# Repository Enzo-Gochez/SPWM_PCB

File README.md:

# SPWM_PCB
A high-precision SPWM control signal generator based on ICL8038 and LT1014. Developed using KiCad, the design includes signal generation, comparison stages, and a robust PCB layout.

Schematic view

PCB layout view

Simulated digital oscilloscope view

3D view

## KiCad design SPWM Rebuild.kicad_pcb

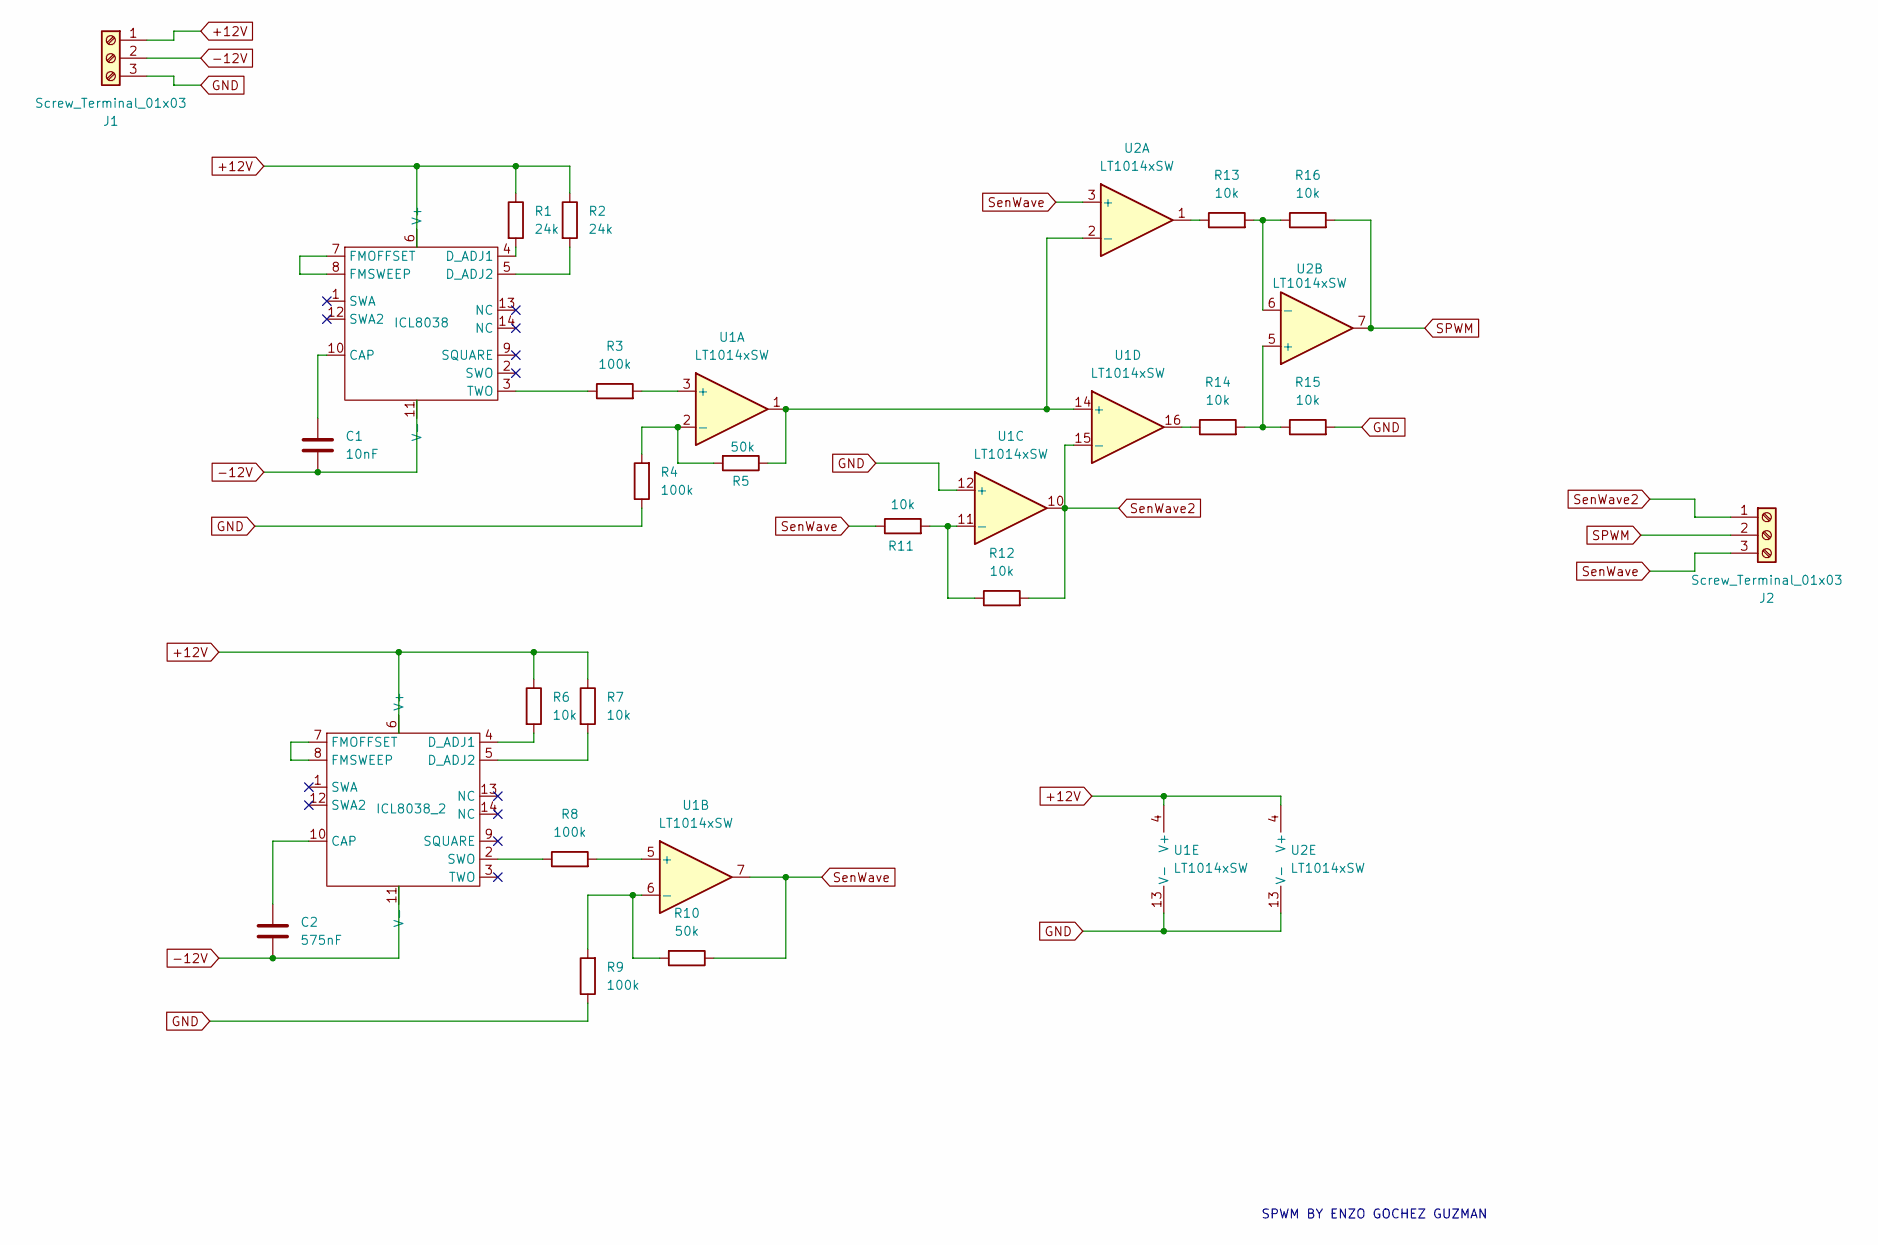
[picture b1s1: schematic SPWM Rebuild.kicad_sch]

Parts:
C1: 10nF; C_Radial_D4.0mm_H7.0mm_P1.50mm
C2: 575nF; C_Radial_D4.0mm_H7.0mm_P1.50mm
ICL8038, ICL8038_2: DIP-14_W7.62mm
J1, J2: Screw_Terminal_01x03; TerminalBlock_Xinya_XY308-2.54-3P_1x03_P2.54mm_Horizontal
R1, R2: 24k; R_Axial_DIN0204_L3.6mm_D1.6mm_P7.62mm_Horizontal
R3, R4, R8, R9: 100k; R_Axial_DIN0204_L3.6mm_D1.6mm_P7.62mm_Horizontal
R5, R10: 50k; R_Axial_DIN0204_L3.6mm_D1.6mm_P7.62mm_Horizontal
R6, R7, R11, R12, R13, R14, R15, R16: 10k; R_Axial_DIN0204_L3.6mm_D1.6mm_P7.62mm_Horizontal
U1: LT1014xSW; DIP-16_W7.62mm
U2: LT1014xSW; SOIC-16W_7.5x10.3mm_P1.27mm

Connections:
+12V: ICL8038.6 (V+), ICL8038_2.6 (V+), J1.1, R1.1, R2.1, R6.1, R7.1, U1.4 (V+), U2.4 (V+); also elsewhere on the board
-12V: C1.2, C2.1, ICL8038.11 (V-), ICL8038_2.11 (V-), J1.2; also elsewhere on the board
GND: J1.3, R4.1, R9.1, R15.2, U1.12 (+), U1.13 (V-), U2.13 (V-); also elsewhere on the board
unnamed: C1.1, ICL8038.10 (CAP)
unnamed: ICL8038.4 (D_ADJ1), R1.2
unnamed: ICL8038.5 (D_ADJ2), R2.2
unnamed: ICL8038.7 (FMOFFSET), ICL8038.8 (FMSWEEP)
unnamed: ICL8038.3 (TWO), R3.1
unnamed: C2.2, ICL8038_2.10 (CAP)
unnamed: ICL8038_2.4 (D_ADJ1), R6.2
unnamed: ICL8038_2.5 (D_ADJ2), R7.2
unnamed: ICL8038_2.7 (FMOFFSET), ICL8038_2.8 (FMSWEEP)
unnamed: ICL8038_2.2 (SWO), R8.1
unnamed: R13.1, U2.1
unnamed: R14.1, U1.16
unnamed: R3.2, U1.3 (+)
unnamed: R4.2, R5.2, U1.2 (-)
unnamed: R8.2, U1.5 (+)
unnamed: R9.2, R10.2, U1.6 (-)
unnamed: R11.2, R12.1, U1.11 (-)
unnamed: R5.1, U1.1, U1.14 (+), U2.2 (-)
unnamed: R14.2, R15.1, U2.5 (+)
unnamed: R13.2, R16.1, U2.6 (-)
SPWM: J2.2, R16.2, U2.7; also elsewhere on the board
SenWave: J2.3, R10.1, R11.1, U1.7, U2.3 (+); also elsewhere on the board
SenWave2: J2.1, R12.2, U1.10, U1.15 (-); also elsewhere on the board

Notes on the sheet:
SPWM BY ENZO GOCHEZ GUZMAN

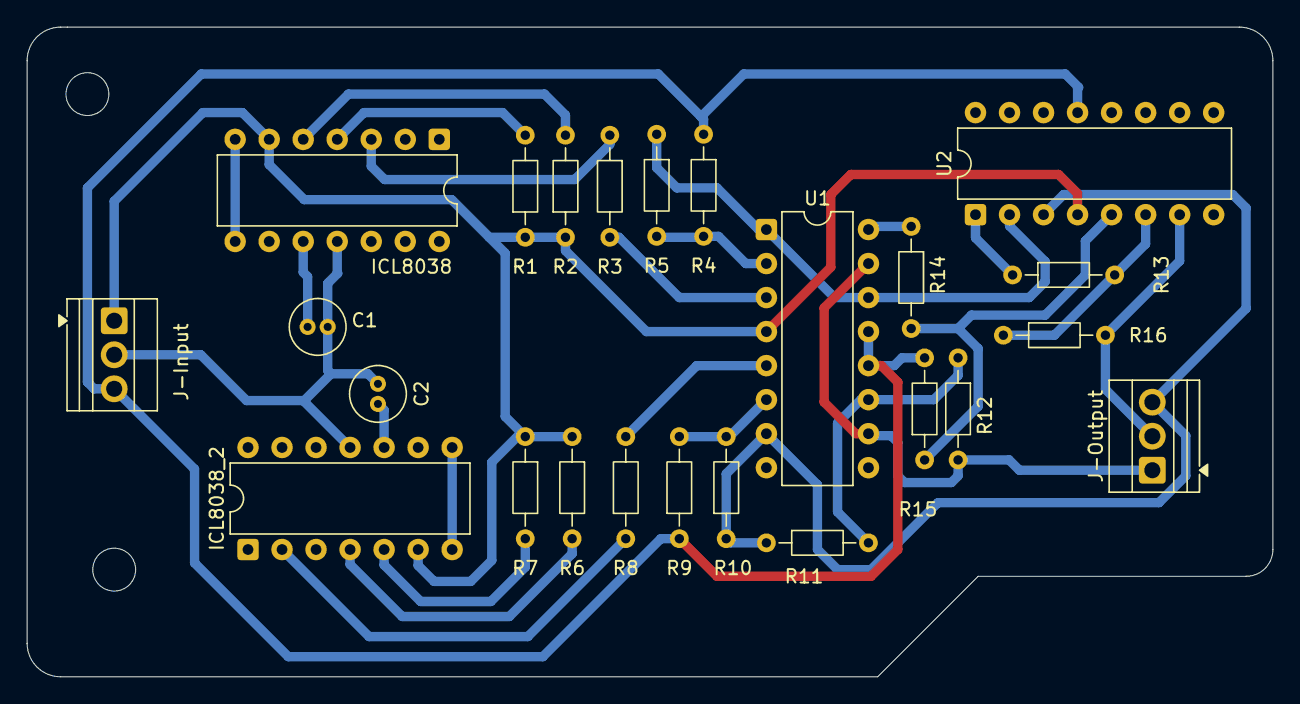
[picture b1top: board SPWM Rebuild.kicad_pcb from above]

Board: 2 copper layers, 93.0 x 48.5 mm, 24 parts (0 on the bottom side), 26 nets.

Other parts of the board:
J-Input: Input Terminal; TerminalBlock_Xinya_XY308-2.54-3P_1x03_P2.54mm_Horizontal
J-Output: Output Terminal; TerminalBlock_Xinya_XY308-2.54-3P_1x03_P2.54mm_Horizontal

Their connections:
+12V: J-Input.1; also elsewhere on the board
-12V: J-Input.2; also elsewhere on the board
GND: J-Input.3; also elsewhere on the board
SPWM: J-Output.2; also elsewhere on the board
SenWave: J-Output.3; also elsewhere on the board
SenWave2: J-Output.1; also elsewhere on the board
